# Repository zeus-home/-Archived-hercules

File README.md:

# Hercules

Hercules is responsible for actually executing the changes in the state of the devices according to the data collected by mercury and decision taken by the tesseract.

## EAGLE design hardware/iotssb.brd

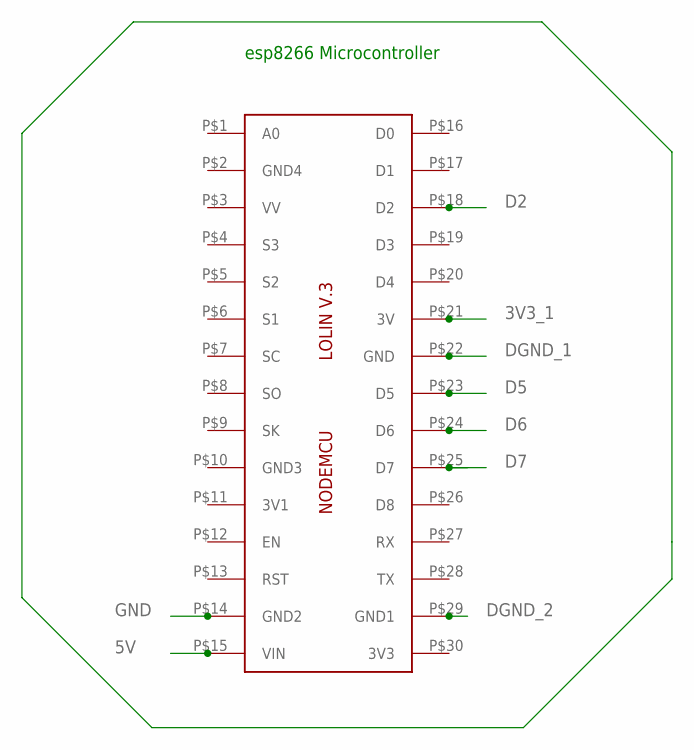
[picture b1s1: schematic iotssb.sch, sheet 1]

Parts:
IC2: LOLINV3ESP12E; LOL1NV0.1

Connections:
3V3_1: IC2.P$21 (3V); also elsewhere on the board
5V: IC2.P$15 (VIN); also elsewhere on the board
D2: IC2.P$18 (D2); also elsewhere on the board
D5: IC2.P$23 (D5); also elsewhere on the board
D6: IC2.P$24 (D6); also elsewhere on the board
D7: IC2.P$25 (D7); also elsewhere on the board
DGND_1: IC2.P$22 (GND); also elsewhere on the board
DGND_2: IC2.P$29 (GND1); also elsewhere on the board
GND: IC2.P$14 (GND2); also elsewhere on the board

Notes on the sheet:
esp8266 Microcontroller

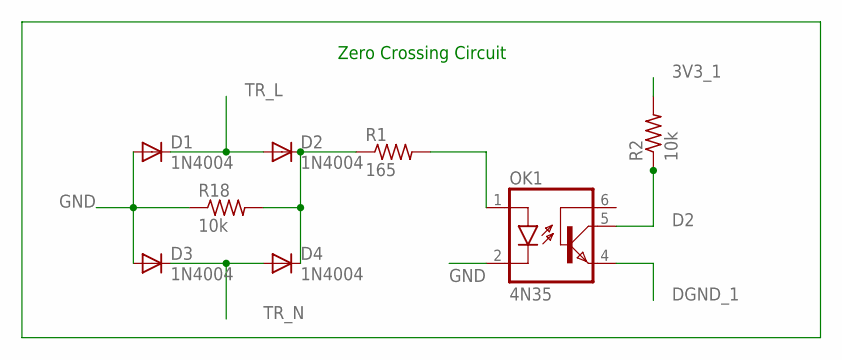
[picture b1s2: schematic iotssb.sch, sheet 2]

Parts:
D1, D2, D3, D4: 1N4004; DO41-10
OK1: 4N35; DIL06
R1: 165; 0207/10
R2, R18: 10k; 0207/10

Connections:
3V3_1: R2.2; also elsewhere on the board
D2: OK1.5 (COL), R2.1; also elsewhere on the board
DGND_1: OK1.4 (EMI); also elsewhere on the board
GND: D1.A, D3.A, OK1.2 (C), R18.1; also elsewhere on the board
unnamed: D2.C, D4.C, R1.1, R18.2
unnamed: OK1.1 (A), R1.2
TR_L: D1.C, D2.A; also elsewhere on the board
TR_N: D3.C, D4.A; also elsewhere on the board

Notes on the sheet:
Zero Crossing Circuit

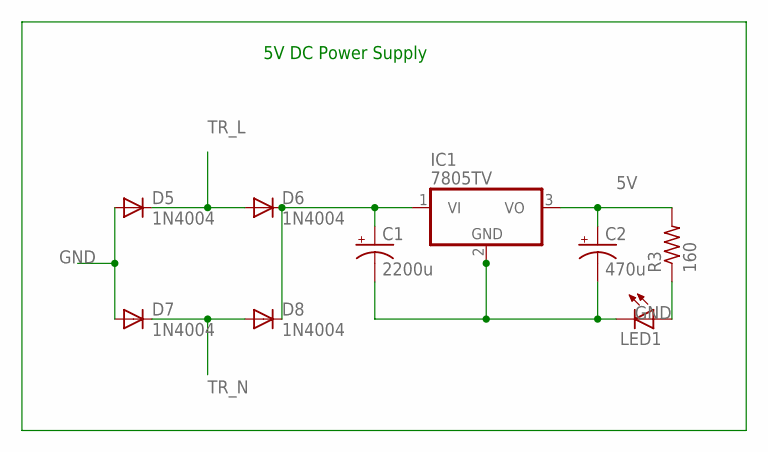
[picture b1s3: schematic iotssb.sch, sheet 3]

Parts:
C1: 2200u; E7,5-18
C2: 470u; E5-13
D5, D6, D7, D8: 1N4004; DO41-10
IC1: 7805TV; TO220V
LED1: LED3MM
R3: 160; 0207/10

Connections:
5V: C2.+, IC1.3 (VO), R3.2; also elsewhere on the board
GND: C1.-, C2.-, D5.A, D7.A, IC1.2 (GND), LED1.K (C); also elsewhere on the board
unnamed: C1.+, D6.C, D8.C, IC1.1 (VI)
unnamed: LED1.A, R3.1
TR_L: D5.C, D6.A; also elsewhere on the board
TR_N: D7.C, D8.A; also elsewhere on the board

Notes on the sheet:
5V DC Power Supply

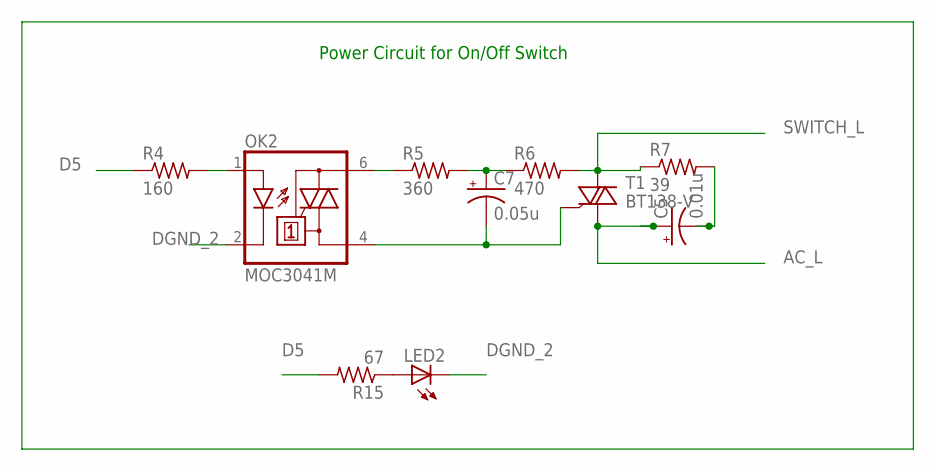
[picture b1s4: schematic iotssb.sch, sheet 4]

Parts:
C5: 0.01u; E5-13
C7: 0.05u; E5-13
LED2: LED3MM
OK2: MOC3041M; DIL06
R4: 160; 0207/10
R5: 360; 0207/15
R6: 470; 0207/15
R7: 39; 0207/15
R15: 67; 0207/10
T1: BT138-V; TO220BV

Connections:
AC_L: C5.+, T1.T1 (A1); also elsewhere on the board
D5: R4.1, R15.2; also elsewhere on the board
DGND_2: LED2.K (C), OK2.2 (C); also elsewhere on the board
unnamed: OK2.6 (A2), R5.1
unnamed: C7.-, OK2.4 (A1), T1.G
unnamed: OK2.1 (A), R4.2
unnamed: C7.+, R5.2, R6.1
unnamed: C5.-, R7.2
unnamed: LED2.A, R15.1
SWITCH_L: R6.2, R7.1, T1.T2 (A2); also elsewhere on the board

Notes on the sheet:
Power Circuit for On/Off Switch

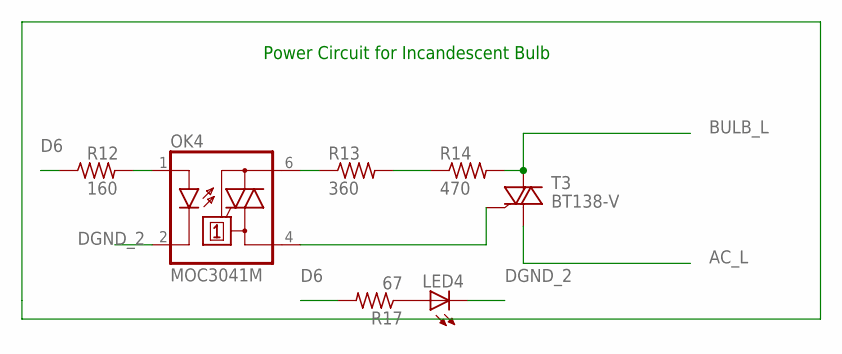
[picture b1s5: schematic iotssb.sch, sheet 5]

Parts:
LED4: LED3MM
OK4: MOC3041M; DIL06
R12: 160; 0207/10
R13: 360; 0207/15
R14: 470; 0207/15
R17: 67; 0207/10
T3: BT138-V; TO220BV

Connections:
AC_L: T3.T1 (A1); also elsewhere on the board
BULB_L: R14.2, T3.T2 (A2); also elsewhere on the board
D6: R12.1, R17.2; also elsewhere on the board
DGND_2: LED4.K (C), OK4.2 (C); also elsewhere on the board
unnamed: OK4.4 (A1), T3.G
unnamed: OK4.1 (A), R12.2
unnamed: OK4.6 (A2), R13.1
unnamed: R13.2, R14.1
unnamed: LED4.A, R17.1

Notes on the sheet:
Power Circuit for Incandescent Bulb

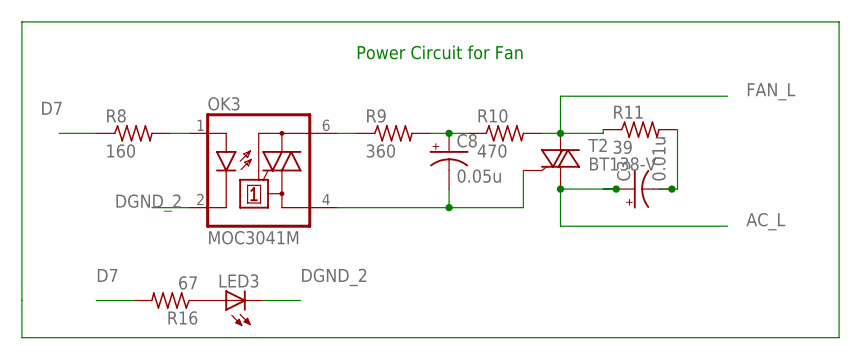
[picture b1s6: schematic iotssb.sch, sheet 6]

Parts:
C3: 0.01u; E5-13
C8: 0.05u; E5-13
LED3: LED3MM
OK3: MOC3041M; DIL06
R8: 160; 0207/10
R9: 360; 0207/15
R10: 470; 0207/15
R11: 39; 0207/15
R16: 67; 0207/10
T2: BT138-V; TO220BV

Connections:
AC_L: C3.+, T2.T1 (A1); also elsewhere on the board
D7: R8.1, R16.2; also elsewhere on the board
DGND_2: LED3.K (C), OK3.2 (C); also elsewhere on the board
FAN_L: R10.2, R11.1, T2.T2 (A2); also elsewhere on the board
unnamed: C8.-, OK3.4 (A1), T2.G
unnamed: OK3.1 (A), R8.2
unnamed: OK3.6 (A2), R9.1
unnamed: C8.+, R9.2, R10.1
unnamed: C3.-, R11.2
unnamed: LED3.A, R16.1

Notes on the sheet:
Power Circuit for Fan

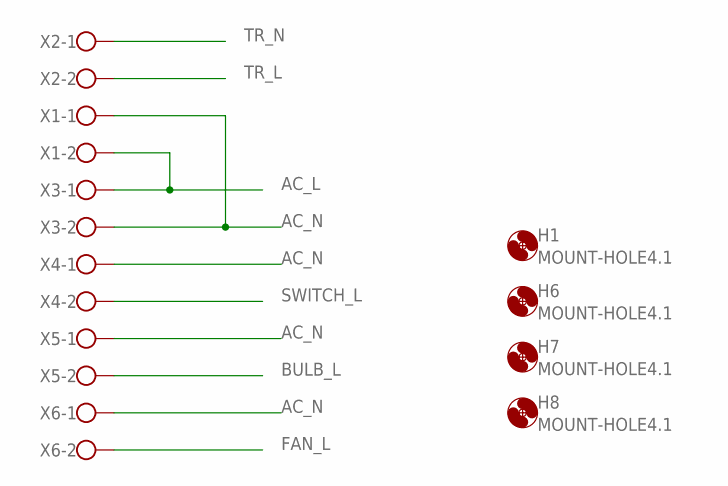
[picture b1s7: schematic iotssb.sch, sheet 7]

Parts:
H1, H6, H7, H8: MOUNT-HOLE4.1; 4,1
X1, X2, X3, X4, X5, X6: W237-102

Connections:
AC_L: X1.2, X3.1; also elsewhere on the board
AC_N: X1.1, X3.2, X4.1, X5.1, X6.1
BULB_L: X5.2; also elsewhere on the board
FAN_L: X6.2; also elsewhere on the board
SWITCH_L: X4.2; also elsewhere on the board
TR_L: X2.2; also elsewhere on the board
TR_N: X2.1; also elsewhere on the board

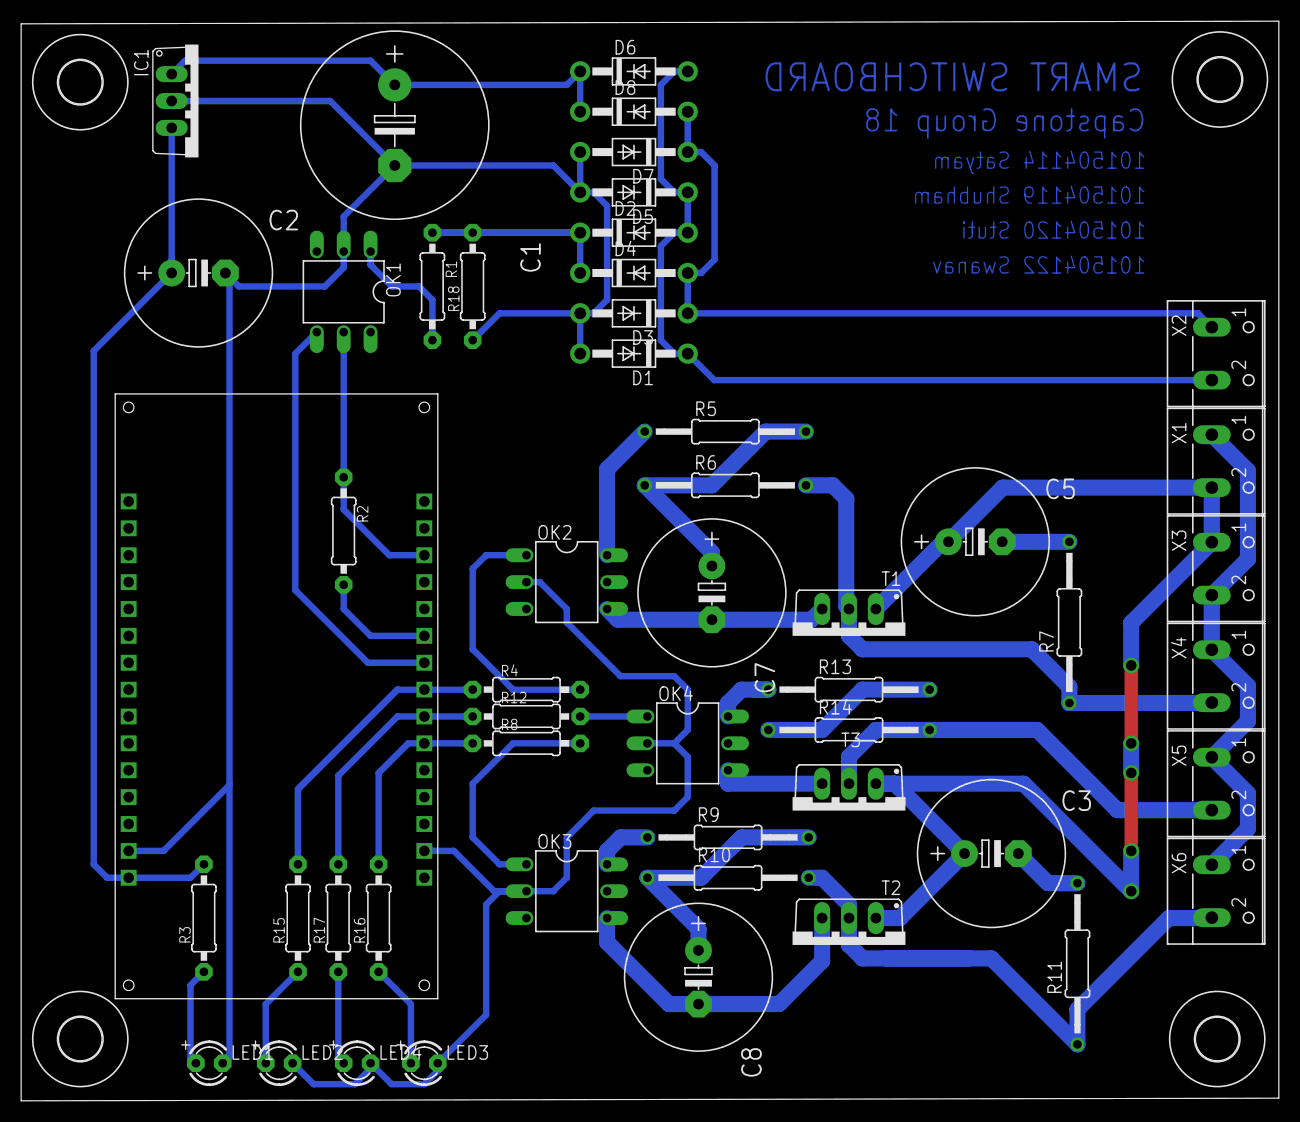
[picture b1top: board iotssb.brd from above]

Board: 2 copper layers, 118.9 x 102.0 mm, 55 parts (0 on the bottom side), 37 nets.

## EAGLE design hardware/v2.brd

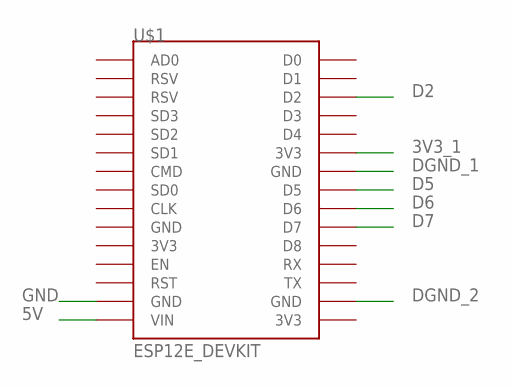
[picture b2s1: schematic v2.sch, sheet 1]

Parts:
U$1: ESP12E_DEVKIT

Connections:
3V3_1: U$1.3V3@1 (3V3); also elsewhere on the board
5V: U$1.VIN; also elsewhere on the board
D2: U$1.D2; also elsewhere on the board
D5: U$1.D5; also elsewhere on the board
D6: U$1.D6; also elsewhere on the board
D7: U$1.D7; also elsewhere on the board
DGND_1: U$1.GND@2 (GND); also elsewhere on the board
DGND_2: U$1.GND@3 (GND); also elsewhere on the board
GND: U$1.GND@1 (GND); also elsewhere on the board

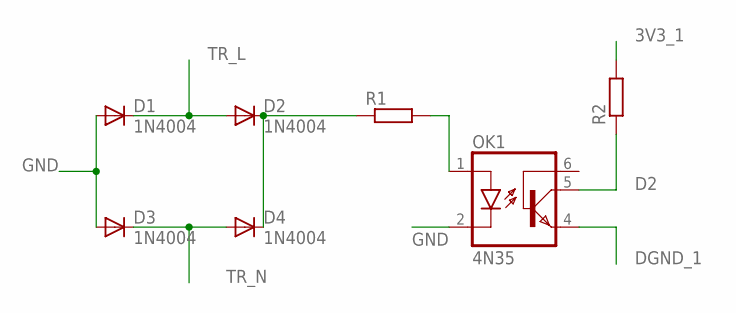
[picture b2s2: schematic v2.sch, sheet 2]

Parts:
D1, D2, D3, D4: 1N4004; DO41-10
OK1: 4N35; DIL06
R1, R2: R0204/7; 0204/7

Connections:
3V3_1: R2.2; also elsewhere on the board
D2: OK1.5 (COL), R2.1; also elsewhere on the board
DGND_1: OK1.4 (EMI); also elsewhere on the board
GND: D1.A, D3.A, OK1.2 (C); also elsewhere on the board
unnamed: D2.C, D4.C, R1.1
unnamed: OK1.1 (A), R1.2
TR_L: D1.C, D2.A; also elsewhere on the board
TR_N: D3.C, D4.A; also elsewhere on the board

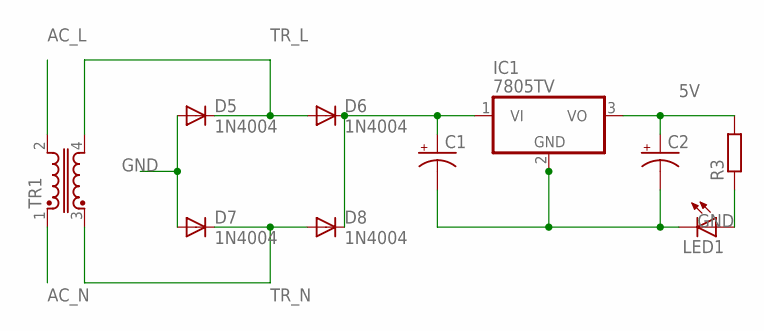
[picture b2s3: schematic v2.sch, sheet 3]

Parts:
C1, C2: CPOL-USE5-13; E5-13
D5, D6, D7, D8: 1N4004; DO41-10
IC1: 7805TV; TO220V
LED1: LED3MM
R3: R0204/7; 0204/7
TR1: U15-TRANSFORMER; U15

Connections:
5V: C2.+, IC1.3 (VO), R3.2; also elsewhere on the board
AC_L: TR1.2; also elsewhere on the board
AC_N: TR1.1; also elsewhere on the board
GND: C1.-, C2.-, D5.A, D7.A, IC1.2 (GND), LED1.K (C); also elsewhere on the board
unnamed: C1.+, D6.C, D8.C, IC1.1 (VI)
unnamed: LED1.A, R3.1
TR_L: D5.C, D6.A, TR1.4; also elsewhere on the board
TR_N: D7.C, D8.A, TR1.3; also elsewhere on the board

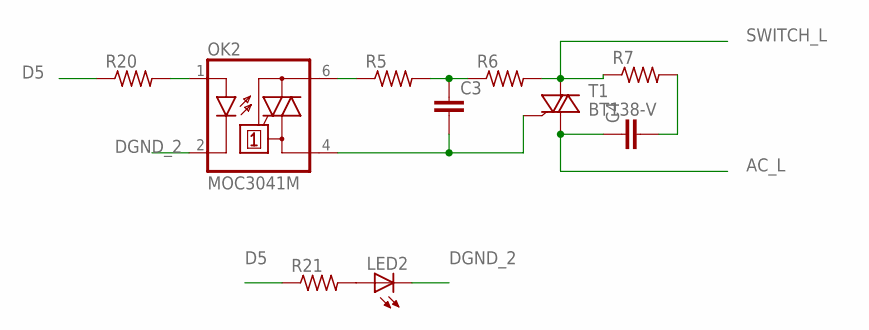
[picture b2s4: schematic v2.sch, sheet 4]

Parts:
C3, C4: C7.5/3; C7.5B3
LED2: LED3MM
OK2: MOC3041M; DIL06
R5, R6, R7, R20, R21: R-US_0207/10; 0207/10
T1: BT138-V; TO220BV

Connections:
AC_L: C4.1, T1.T1 (A1); also elsewhere on the board
D5: R20.1, R21.1; also elsewhere on the board
DGND_2: LED2.K (C), OK2.2 (C); also elsewhere on the board
unnamed: OK2.6 (A2), R5.1
unnamed: C3.2, OK2.4 (A1), T1.G
unnamed: OK2.1 (A), R20.2
unnamed: C3.1, R5.2, R6.1
unnamed: C4.2, R7.2
unnamed: LED2.A, R21.2
SWITCH_L: R6.2, R7.1, T1.T2 (A2); also elsewhere on the board

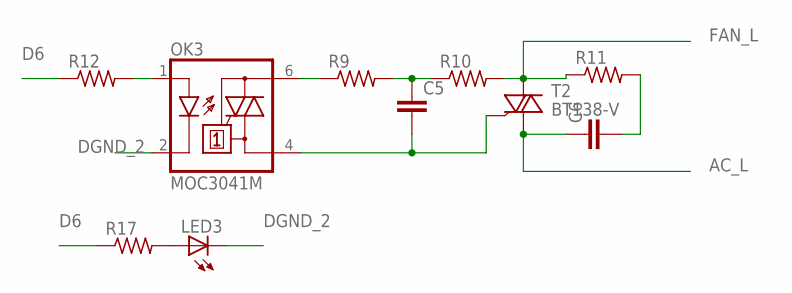
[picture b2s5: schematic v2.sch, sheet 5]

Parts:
C5, C6: C7.5/3; C7.5B3
LED3: LED3MM
OK3: MOC3041M; DIL06
R9, R10, R11, R12, R17: R-US_0207/10; 0207/10
T2: BT138-V; TO220BV

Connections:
AC_L: C6.1, T2.T1 (A1); also elsewhere on the board
D6: R12.1, R17.1; also elsewhere on the board
DGND_2: LED3.K (C), OK3.2 (C); also elsewhere on the board
FAN_L: R10.2, R11.1, T2.T2 (A2); also elsewhere on the board
unnamed: C5.2, OK3.4 (A1), T2.G
unnamed: OK3.1 (A), R12.2
unnamed: OK3.6 (A2), R9.1
unnamed: C5.1, R9.2, R10.1
unnamed: C6.2, R11.2
unnamed: LED3.A, R17.2

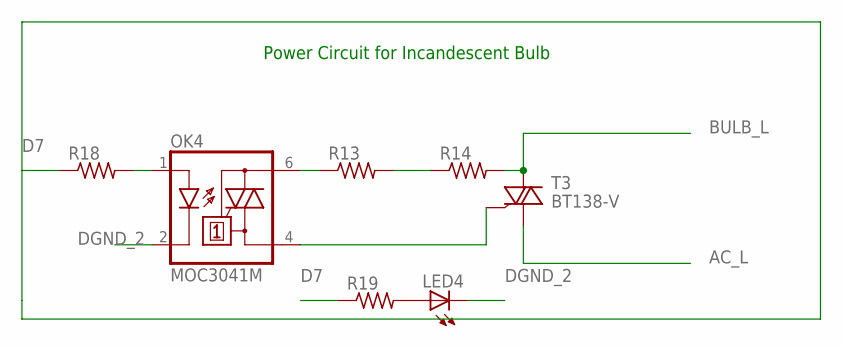
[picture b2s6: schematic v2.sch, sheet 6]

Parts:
LED4: LED3MM
OK4: MOC3041M; DIL06
R13, R14, R18, R19: R-US_0207/10; 0207/10
T3: BT138-V; TO220BV

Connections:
AC_L: T3.T1 (A1); also elsewhere on the board
BULB_L: R14.2, T3.T2 (A2); also elsewhere on the board
D7: R18.1, R19.1; also elsewhere on the board
DGND_2: LED4.K (C), OK4.2 (C); also elsewhere on the board
unnamed: OK4.4 (A1), T3.G
unnamed: OK4.1 (A), R18.2
unnamed: OK4.6 (A2), R13.1
unnamed: R13.2, R14.1
unnamed: LED4.A, R19.2

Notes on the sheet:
Power Circuit for Incandescent Bulb

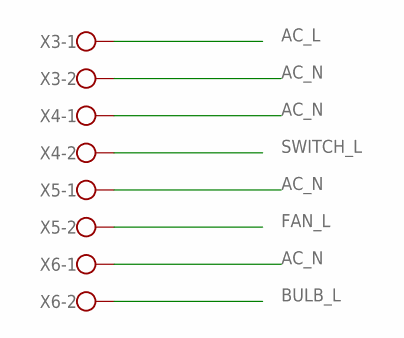
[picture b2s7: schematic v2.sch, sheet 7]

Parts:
X3, X4, X5, X6: W237-102

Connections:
AC_L: X3.1; also elsewhere on the board
AC_N: X3.2, X4.1, X5.1, X6.1; also elsewhere on the board
BULB_L: X6.2; also elsewhere on the board
FAN_L: X5.2; also elsewhere on the board
SWITCH_L: X4.2; also elsewhere on the board

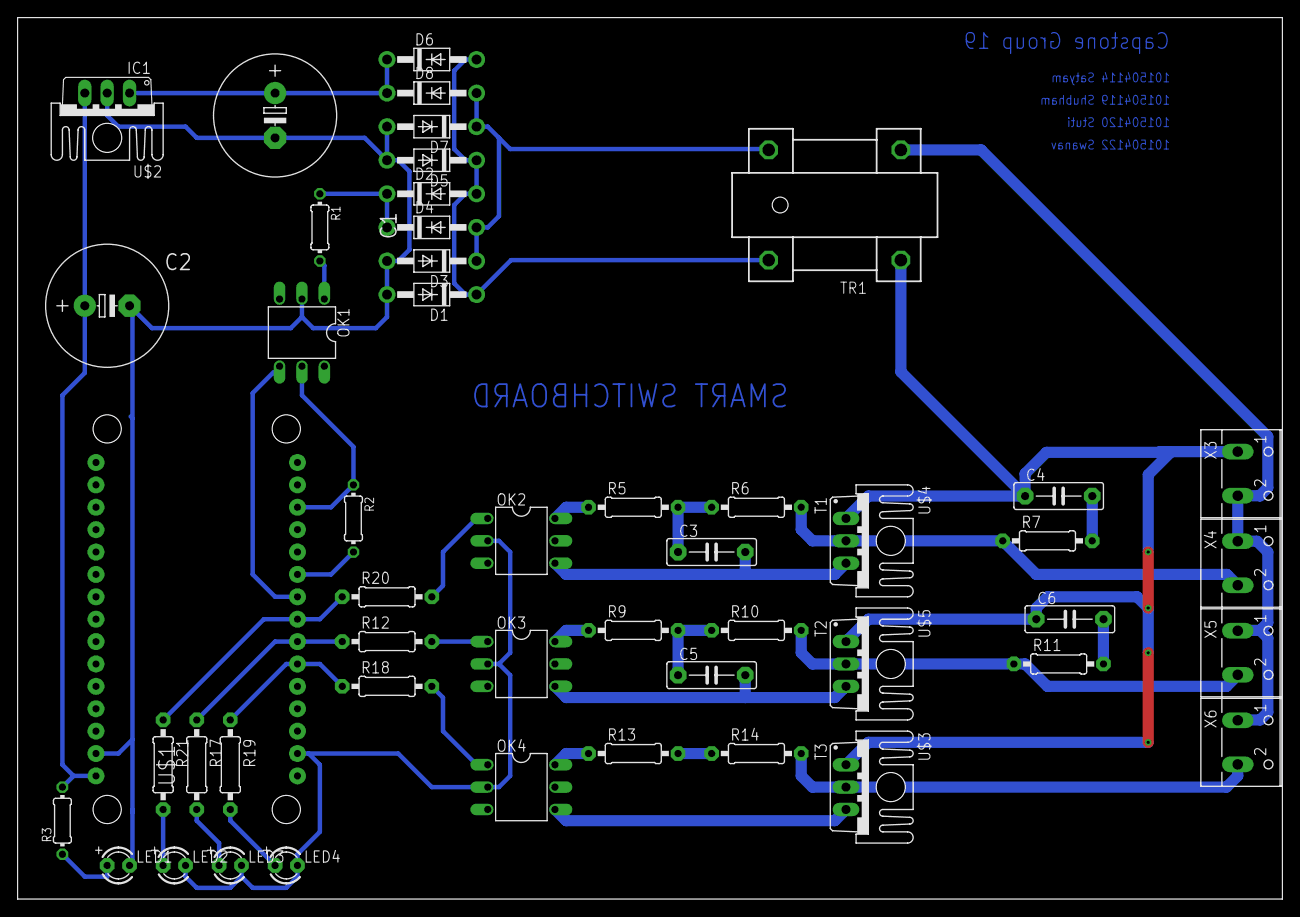
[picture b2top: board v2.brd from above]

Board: 2 copper layers, 143.5 x 100.0 mm, 53 parts (0 on the bottom side), 37 nets.

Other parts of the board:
U$2, U$3, U$4, U$5: SK95-2M3

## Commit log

2018-06-11 Refactoring.
2018-06-11 README added.
2018-06-12 README added
2018-06-28 Switch Board Module created.
2018-06-28 README for Fan modified.
2018-07-13 Flutter mobile app created.
2018-08-03 Moved mobile_app to a new repository; Edison
2018-08-11 Hercules Module updated.
2018-08-11 Basic functionality implemented.
2018-08-12 Mqtt Implemented, with Reset button functionality.
2018-08-12 Debugging added.
2018-08-16 Refactoring all modules in one
2018-08-16 Integrate Travis CI
2018-08-16 PubSubClient dependency added.
2018-08-16 Added Travis CI build icon.
2018-08-25 Indicator use timer instead of delay.
2018-08-25 Subtle changes
2018-08-25 Firing circuit.
2018-09-20 Hercules ID integration.
2018-09-20 Fixed Reset Button definition.
2018-09-20 Fixed Reset Button functionality.
2018-09-20 Removed deprecated string warnings.
2018-10-02 Removed boilerplate CI Code
2018-12-06 Working platform
2018-12-10 Eagle Project added.
